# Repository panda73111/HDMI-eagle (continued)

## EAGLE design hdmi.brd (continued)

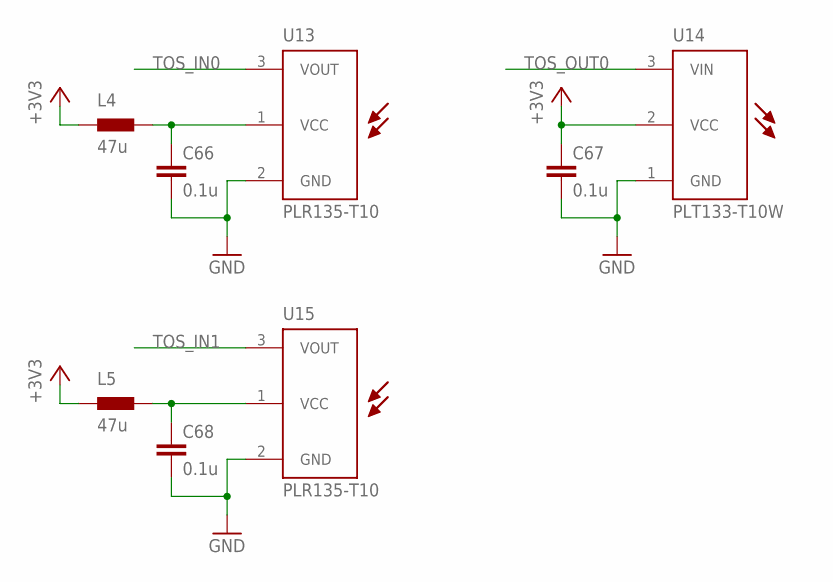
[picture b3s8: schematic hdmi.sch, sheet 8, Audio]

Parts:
C66, C67, C68: 0.1u; 0402
L4, L5: 47u; 0603
U13, U15: PLR135-T10; PLR135-T10_PLT133-T10W
U14: PLT133-T10W; PLR135-T10_PLT133-T10W

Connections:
+3V3: C67.1, L4.1, L5.1, U14.2 (VCC); also elsewhere on the board
GND: C66.2, C67.2, C68.2, U13.2 (GND), U14.1 (GND), U15.2 (GND); also elsewhere on the board
unnamed: C68.1, L5.2, U15.1 (VCC)
unnamed: C66.1, L4.2, U13.1 (VCC)
TOS_IN0: U13.3 (VOUT); also elsewhere on the board
TOS_IN1: U15.3 (VOUT); also elsewhere on the board
TOS_OUT0: U14.3 (VIN); also elsewhere on the board

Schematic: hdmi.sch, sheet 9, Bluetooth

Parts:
C69, C70: 0.1u; 0402
R46, R47: 10k; 0402
U16, U17: TP10SQ
U18: PAN1322

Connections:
+3V3: C69.1, C70.1, R46.2, U18.A4 (VSUPPLY), U18.A5 (VSUPPLY), U18.A6 (VSUPPLY), U18.B5 (ONOFF), U18.C5 (VDD1), U18.F6 (VDDUART); also elsewhere on the board
BT_CTS: U18.F5 (P0.7_UARTCTS); also elsewhere on the board
BT_RESET#: R47.2, U18.A3 (RESET#); also elsewhere on the board
BT_RTS: U18.F8 (P0.6_UARTRTS); also elsewhere on the board
BT_RX: U18.E6 (P0.5_UARTRXD); also elsewhere on the board
BT_TX: U18.F7 (P0.4_UARTTXD); also elsewhere on the board
BT_WAKE: R46.1, U18.F4 (P0.14_LPMIN); also elsewhere on the board
GND: C69.2, C70.2, R47.1, U18.A1 (VSS), U18.A7 (VSS), U18.A9 (VSS), U18.A11 (VSS), U18.A12 (VSS), U18.C8 (VSS), U18.C9 (VSS), U18.D7 (VSS), U18.D8 (VSS), U18.E8 (VSS), U18.E9 (VSS), U18.F1 (VSS), U18.F9 (VSS), U18.F11 (VSS), U18.F12 (VSS); also elsewhere on the board
unnamed: U17.TP, U18.E1 (P0.12_SDA0)
unnamed: U16.TP, U18.E2 (P0.13_SCL0)

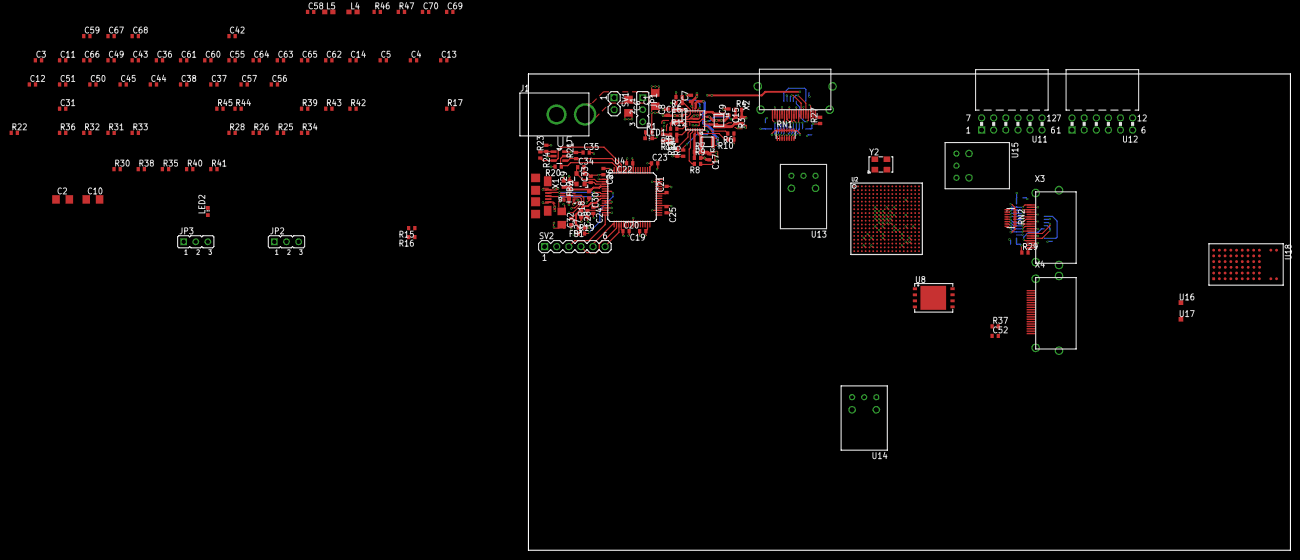
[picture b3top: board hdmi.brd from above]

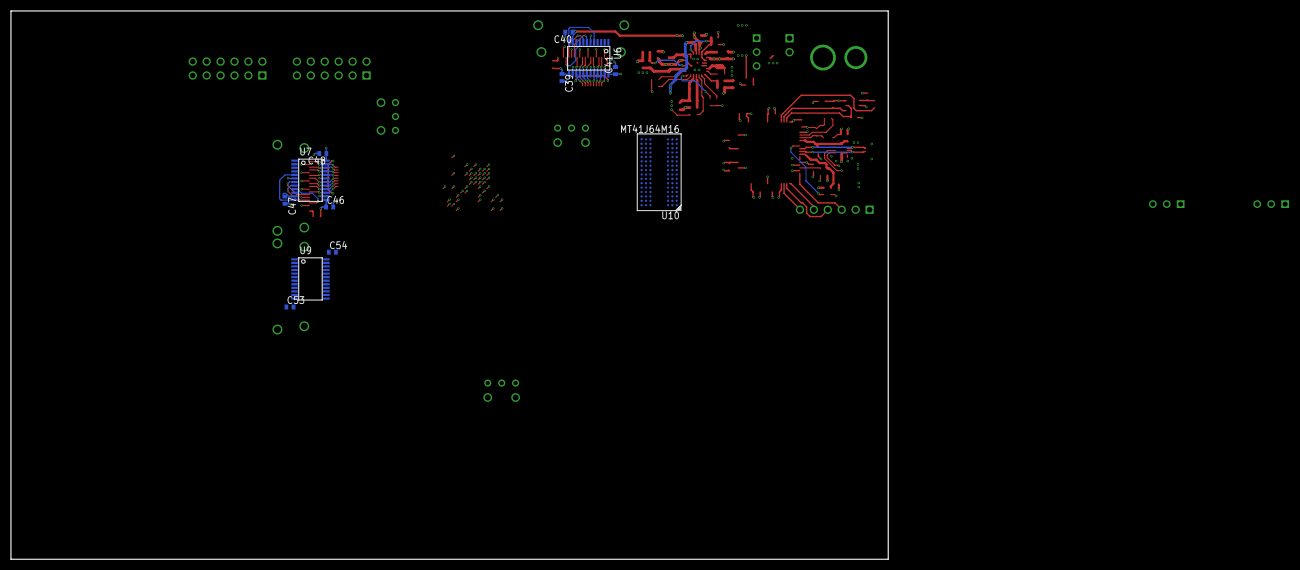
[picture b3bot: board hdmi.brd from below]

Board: 4 copper layers, 160.0 x 100.0 mm, 158 parts (12 on the bottom side), 202 nets.

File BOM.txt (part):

Stückliste exportiert aus D:/GitHub/pandaLight-eagle/pandaLight.sch am 02.06.2014 14:51:41

Qty Value             Device            Package                Parts                                                                                                                                                     Description                                                          
31  0.1u              CAPACITOR0402     0402                   C19, C20, C21, C22, C24, C25, C26, C28, C30, C35, C39, C40, C41, C42, C46, C47, C48, C52, C53, C54, C60, C61, C62, C63, C64, C65, C66, C67, C68, C69, C70 generic capacitor                                                    
13  0.47u             CAPACITOR0402     0402                   C4, C5, C12, C13, C14, C37, C38, C44, C45, C50, C51, C56, C57                                                                                             generic capacitor                                                    
4   100               RESISTOR0402      0402                   R2, R32, R36, R43                                                                                                                                         generic resistor                                                     
5   100u              CAPACITOR1206     1206                   C1, C2, C6, C10, C32                                                                                                                                      generic capacitor                                                    
20  10k               RESISTOR0402      0402                   R5, R6, R8, R10, R12, R14, R15, R17, R18, R20, R21, R22, R23, R26, R28, R31, R33, R37, R46, R47                                                           generic resistor                                                     
3   10u               CAPACITOR0402     0402                   C7, C8, C9                                                                                                                                                generic capacitor                                                    
1   120               RESISTOR0402      0402                   R39                                                                                                                                                       generic resistor                                                     
1   12k               RESISTOR0402      0402                   R19                                                                                                                                                       generic resistor                                                     
2   1A                FERRITE0402       0402                   FB1, FB2                                                                                                                                                  generic ferrite bead                                                 
8   1k                RESISTOR0402      0402                   R1, R16, R25, R27, R29, R34, R44, R45                                                                                                                     generic resistor                                                     
2   1u                CAPACITOR0402     0402                   C58, C59                                                                                                                                                  generic capacitor                                                    
3   1u, 3A            INDUCTOR1008      1008                   L1, L2, L3                                                                                                                                                generic inductor                                                     
1   2.4k              RESISTOR0402      0402                   R30                                                                                                                                                       generic resistor                                                     
1   20Mhz             636               636                    Y2                                                                                                                                                        HCMOS/TTL clock oscillator                                           
1   221k              RESISTOR0402      0402                   R9                                                                                                                                                        generic resistor                                                     
1   240               RESISTOR0402      0402                   R42                                                                                                                                                       generic resistor                                                     
1   274k              RESISTOR0402      0402                   R11                                                                                                                                                       generic resistor                                                     
2   27p               CAPACITOR0402     0402                   C33, C34                                                                                                                                                  generic capacitor                                                    
1   294k              RESISTOR0402      0402                   R13                                                                                                                                                       generic resistor                                                     
1   2k2               RESISTOR0402      0402                   R24                                                                                                                                                       generic resistor                                                     
1   309k              RESISTOR0402      0402                   R3                                                                                                                                                        generic resistor                                                     
1   316k              RESISTOR0402      0402                   R7                                                                                                                                                        generic resistor                                                     
4   4.7k              RESISTOR0402      0402                   R35, R38, R40, R41                                                                                                                                        generic resistor                                                     
14  4.7u              CAPACITOR0402     0402                   C3, C11, C15, C16, C17, C18, C23, C27, C29, C31, C36, C43, C49, C55                                                                                       generic capacitor                                                    
1   403               403               403-3.2X2.5            Y1                                                                                                                                                        Surface Mount Quartz Crystal                                         
2   47u               INDUCTOR0603      0603                   L4, L5                                                                                                                                                    generic inductor                                                     
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
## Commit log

2014-03-05 +prj-hdmi.lbr, +5V protection
2014-03-05 began mergin and cleaning up libraries
2014-03-06 +5V supply zener diode and minor misc. changes
2014-03-07 +N-MOSFET at 5V supply, HDMI connector pin swap, minor wiring changes
2014-03-07 Delete eagle.epf
    This should have been ignored...
2014-03-07 fixed .gitignore (trailing space
2014-03-08 +Oscillator
2014-03-10 switched from hot swap controller to buck regulator, +PMOD
2014-03-10 minor schematic placement changes
2014-03-13 +Toslink
2014-04-01 +Toslink connections
2014-04-15 +Schematic notes
2014-05-08 Removed regulator for external power, schematics look good I think
2014-05-10 Slight schematic part relocations
2014-05-11 +Bluetooth module
2014-05-12 Began moving components in the board layout
2014-05-12 +First layout of power management
2014-05-12 Moved bypass capacitors at the power management to the top layer
2014-05-13 Rerouted USB, added more bypass capacitors at the FT2232H
2014-05-13 More USB related routing
2014-05-14 Changed FT2232H from package QFN to LQFP; Finished first routing of power management and USB
2014-05-16 Moved chips to their general direction
2014-05-17 Switched HDMI companion chip package, finished routing of the first HDMI group
2014-05-18 Switched all parts to the version of prj-hdmi.lbr; Corrected the "+5V" ping naming conflict; Exported BOM.xlsx
2014-05-19 Customized some of the library parts
2014-05-22 Device management
2014-05-24 some more library cleanup
2014-05-27 finished cleanup of library components
2014-05-27 Changed FT2232H crystal
2014-05-29 Routed HDMI_RX1
2014-05-30 Corrected some library/schemantic inconsistencies due to device renaming; Renamed and numbered all devices in order of placement using the library prefix
2014-05-30 Re-Exported the library, getting rid of all unused packages and symbols
2014-05-30 Added *.scr to .gitignore
2014-06-01 Changed project name and file names to "pandaLight"; Routed connections FPGA to oscillator and HDMI_RX0
2014-06-03 Began adding BOM-ex parts
2014-06-04 Switched to an available DDR3 SDRAM chip; Finished first BOM-ex; Matched the length of the HDMI RX0 traces
2014-06-04 Switched the buck regulator to an available one; Corrected wrong packages and BOM-ex
2014-06-04 Routed the new buck regulator
2014-06-10 Corrected the FPGA placement and routing the its ball pitch
2014-06-10 Temporarily unconnected the PMOD and USB to FPGA wires; Moved power management and USB a little closer together; Began routing HDMI_RX1
2014-06-11 Began length matching the HDMI_RX1 traces
2014-06-13 Finished first routing of HDMI_RX1; Corrected some traces and placements
2014-06-13 Straightened some via stubs
2014-06-13 Moved the FPGA to the center of the PCB, which is now 10mm x 5mm in size
2014-06-13 Actually resized the board; Tweaked some FT223H related traces
2014-06-14 Set polygon sizes from 0 to 5mil (for later GERBER generation)
2014-06-14 Placed some bypass capacitors
2014-06-14 Routed blutooth module
2014-06-14 Corrected the blutooth module's footprint being slighty misaligned
2014-06-14 First routing of the serial flash; Placed some more bypass capacitors
2014-06-15 Routed HDMI_TX0; Placed the PMODs to the board's bottom left edge
2014-06-15 Switched the 1*8 resistor networks with 2*4 ones; Moved the HDMI_RX0 nets to the top layer
2014-06-15 Finished moving the HDMI_RX0 traces to the top layer; Began doing the same with the HDMI_RX1 traces
2014-06-16 Finished putting the HDMI_RX1 traces on the top layer
2014-06-16 Forgot some vias at HDMI_RX1
2014-06-16 Tried the differential routing and the meander
2014-06-17 Used the meander on the HDMI_RX1 traces
2014-06-19 Moved the pullup resistor networks and removed vias from the HDMI_RX* traces
2014-06-19 Began routing the DDR3 RAM
2014-06-21 First routing of the DDR3 address lines
2014-06-22 Finished routing the first DDR3 signal group: A* BA* RAS# CAS# WE#, now to length matching that group...
2014-06-23 Some tweaking and length matching of the DDR3 traces
2014-06-23 Four signals of the DDR3 address signal group length matched!
2014-06-23 Length matched a whole lot of signals!
2014-06-23 Finished length matching the DDR3 address trace group!
2014-06-26 NEEDS MOVING OF THE RX HDMI CLOCK CHANNELS TO DIFFERENTIAL GLOBAL CLOCK INPUTS!!
2014-08-20 pandaLight -> pandaLightPlus; New board: smaller, LX9 FPGA
2014-08-21 Continued switching to LX9
2014-08-22 Made new signal connections; Removed old signals; New buck regulator; Reset the board layout
2014-08-24 Created BOM; Began routing; Changed to available LEDs
2014-08-25 Little bit of routing
2014-08-25 Removed the USB companion chip; Routed USB part
2014-08-26 Routed HDMI TX
2014-08-26 Minor library changes; Searching for CMOS to TTL level shifters for the LED strip outputs
2014-08-27 Minor changes; Still looking for decent pin protection
2014-08-28 Added LED signal CMOS to TTL level shifter
2014-08-31 Added second LED strip connector; Switched to 4-Bit level shifter
2014-08-31 Routed HDMI RX
2014-08-31 Adjusted the board size; Approximately placed the larger components
2014-08-31 Minor routing
2014-09-01 Routed USB to FPGA signals
2014-09-01 Routed PMODs
2014-09-03 Switched 3.3V with ground layer (now ground is on top); Adjusted board width to 90mm; Routed everything, about 10 airwires left!
2014-09-03 No more airwires! Added ESD protection at 5V_SUP
2014-09-03 Move S6LX9 to own library; Adjusted parts' "place" layer; USB_PWRSAV#
2014-09-04 Part renumber; "place" layer changes
2014-09-05 Changed all 7mil traces to 6mil; Set library part prefixes; Applied all part attributes
2014-09-08 Major design change: I remembered multiboot! That makes it possible to use two HDMI receivers again! So I removed the SPDI/Fs, for which there was no more space, and I added the HDMI receptical and r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
2014-09-08 Added Feducias; Added logos; Minor silkscreen changes
2014-09-09 Adjusted and placed part names; refreshed BOM
2014-09-10 Moved names awaay from the pads a little; added port descriptions
2014-09-10 Added HDMI port arrows
2014-09-28 Corrected wrong BOMex part number of the inductors (after ordering them...); Switched to smaller 0402, 0603, 1206 footprint: Many of my hand placed passives are crooked; Moved all names away from vias
2014-09-29 Trying EagleUp; Now using R* and C* parts for caps and resistors
2014-09-29 First draft of SketchUp model; Set extra part for ferrite beads
2014-09-29 Forgot saving
2014-10-05 Corrected wrongly aligned HDMI connector; First version of SketchUp render, only the bluetooth module is missing
2014-10-06 Updated SketchUp model, all parts present
2014-10-12 Changed buck regulator and level translator to SOT packages, yet unrouted
2014-10-13 Routed new buck regulator
2014-10-13 Routed everything, corrected unconnected ground pins (due to higher isolation)
2014-10-14 Minor improvements of labels
2014-10-14 Finalized rev.1 design; Exported new BOM; rendered new SketchUp model
2014-11-09 Final rev.1 silksreen adjustments; Generated final BOM & partlist; Added Seeedstudio gerber files
2015-01-06 Corrected LEDs control wiring error
2015-11-02 Added Collada model file
2015-11-02 Added renders
2015-11-02 Added README showing render
2015-11-02 Forgot textures for Collada file
2015-11-02 Changed a render
2015-11-02 Added link to 3D Warehouse
2017-02-08 Newer .gitignore from gitignore.io
2017-02-08 Added part ESP-WROOM-32 to the library
2017-02-08 Added description to ESP-WROOM-32
2017-02-08 Moved pins of ESP-WROOM-32
2017-02-08 Replaced PAN1322 with ESP-WROOM-32
    Connected it to UART and JTAG; Began routing
2017-02-09 Added borders to all capacitor and resistor packages
2017-02-10 Routed some of the HDMI signals
2017-02-20 Added tPlace to ESP-32
2017-02-20 Finished routing HDMI RX1 and ESP-32
2017-02-20 Rotated bottom labels; Minor routing changes
2017-02-20 5V polygon size adjustment
2017-02-20 Fixed ESP32 south pad placement
2017-02-20 rev.2; Logo beams on tStop layer
2017-02-20 Exported rev.2 Gerber files
2017-02-20 Added missing _tSilk layer to Gerber export
2017-02-20 Showing dimension units
2017-02-20 Added ESP_EN and ESP_IO0 to FPGA for programming the ESP32
2017-02-20 Rerouted HDMI RX1 signals
2017-02-20 New Gerber export
